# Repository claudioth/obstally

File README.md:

# OBS Tally & Control
OBS Tallylights via OBS-Websockets and GPIOzero.

This Toolset was written to support sundays-church-streaming

## Simplicity
On church a lot of work is done by voluntiers, so we can not exspect deep
network and computer knowhow. 

So the tool is written automatically fix problems as much as possible.

Example:
* problem: the network connection to OBS ist lost
* auto-reaction: try to reconnect to OBS automaticaly

## Enviroment
The tool was written for the following context:
* runs on a raspberry pi (or probably any linux computer)
* OBS ist best used in "studio mode", but "none studio" should also work
  (but will not react when changing visibility of sources of a scene in program)

## Features
* configuration by real XML, not depenting on tag ordering
* LEDs status can be configured in dependence of scenes and/or sources
* support unlimited amount of scene and sources
* after startup LEDs will proactive be set conforming actual OBS status
  (will not wait for first switch/preview event)
* connection to OBS is monitored and will try to reconnect if lost
* start order is uncritical, OBS can be (re-)started anytime
* if not connected all CAM LEDs are switched on
* (optional) connection status can be visualized by an extra LED

## LED colors
LED colors depends (of course) on your personal hardware configuration.

Wie use a blue LED to visualise the connection status:
* blinking: not connected, trying to reconnect
* permanently glowing: connected

We use for each CAM, 2 LEDs with following colors:
* red LED for "in program"
* orange LED for "in preview"

### possible LEDs glowing combinations
The behavior is configurable. You can choose one of the following, conforming 
your preference and needs:

* (A) basic:in basic-mode any conbination is possible, also both LEDs on at the same time
    - CAM in programm => red LED glowing
    - CAM in preview => orange LED glowing

* (B) max. 1 LED per CAM enabled: same as (A), but in case a CAM is also "in preview", only the
    "in program" LED will be enabled

* (C) max. 1 LED type enabled: same as (B), but maximal 1 LED type will be enabled at the same time.
    examples:
     - CAM 1 in program AND CAM 2 in preview: only LED for CAM 1 will be enabled
     - unknown scene/source in program AND CAM 1 in preview: CAM 1 LED shown
     - CAM 1 and CAM 2 in program, CAM 3 in preview: CAM 1+2 will be enabled
     - unknown scene/source in program AND CAM 1+2 in preview: CAM 1+2 LED shown

### Installation
### automated
In the sufolder "install" is a script that can be used for automatical installation

#### manually
If you prefere to install it manually, here a list of todos:
* install all needed third-party-software

```shell
apt update
apt install nginx php-fpm php-xml python-gpiozero
pip install obs-websocket-py
git checkout https://github.com/claudioth/obstally
```
* setup your NGINX to support PHP-scripts
* link or copy the content of the "www" subfolder to your webfolder

```shell
mkdir /var/www/html/tally/
cp -r ./www/* /var/www/html/tally/
```
* Call the index.php from your browser to configure this tool

    http://localhost/tally/

* Setup OBS-Tally Settings (IP, password, port from OBS-Websockets, scenes, sources and GPIO-Ports)
* Connect LEDs to the matching GPIO and try
* If you want to use OBSTally with an relais-card, you need to use the Inverted-Version
* install this script as a service to automatically startup when booting your raspberry

### Configuration
The configuration is done by editing the XML-file.

**Attention:** each GPIO port can only be used *once*

**Hint:** the GPIO port can also be inverted. Just add an attribute to the tag 
(`inverted="true"`) or simple set a - before the GPIO number.

#### obswebsocket
Here are the connection settings to OBS defined
* `host`: The hostname or IP-address to connect to
    - in case an attribute `network` is given, the host value will only be used, if the own IP matches to the given network.
    All not matching networks will be ignored.
    - A mix of both is possible, if not matching network was found, than the value without attribute will be used as fallback.
	  
* `port`: (optional) the port to be used for connection, by default 4444
* `pass`: (optional) a password for connection authentication, default is empty
* `gpio_connected`: a GPIO number where a LED could be connected to visualise
  the connection-status:
    - *off*: service ist not running
    - *flashing*: trying to connect to OBS
    - *on*: connected to OBS

```xml
	<obswebsocket>
		<host>192.168.2.137</host> <!-- default host -->
		<!-- but the following would be used if network matches -->
		<host network="192.168.10">192.168.10.137</host>
		<port>4444</port>
		<pass/>
		<gpio_connected>19</gpio_connected>
	</obswebsocket>
```

#### scene
You can define several scene to LED combinations. Each scene is defined by:
* `name`: then name of the OBS scene
* `gpio_preview`: a GPIO number where a LED is connected to show,
  that the scene is actualy been shown in the "preview". 
* `gpio_program`: a GPIO number where a LED is connected to show,
  that the scene is actualy been shown in the "program". 

```XML
	<scene>
		<name>HDMI 1</name>
		<gpio_preview>2</gpio_preview>
		<gpio_program>3</gpio_program>
	</scene>
	<scene>
		<!-- example for use inverted signals -->
		<name>HDMI 2</name>
		<gpio_preview>-4</gpio_preview>
		<gpio_program inverted="true">5</gpio_program>
	</scene>
```

#### source
You can define several source to LED combinations. Each source is defined by:
* `name`: then name of the OBS source
* `gpio_preview`: a GPIO number where a LED is connected to show,
  that the scene is actualy been shown in the "preview". 
* `gpio_program`: a GPIO number where a LED is connected to show,
  that the scene is actualy been shown in the "program". 

```XML
	<source>
		<name>PTZ1</name>
		<gpio_preview>26</gpio_preview>
		<gpio_program>6</gpio_program>
	</source>
	<source>
		<!-- example for use inverted signals -->
		<name>PTZ2</name>
		<gpio_preview>-20</gpio_preview>
		<gpio_program inverted="true">12</gpio_program>
	</source>
```
### License
This program is free software: you can redistribute it and/or modify
it under the terms of the GNU General Public License as published by
the Free Software Foundation, either version 3 of the License, or
(at your option) any later version.

This program is distributed in the hope that it will be useful,
but WITHOUT ANY WARRANTY; without even the implied warranty of
MERCHANTABILITY or FITNESS FOR A PARTICULAR PURPOSE.  See the
GNU General Public License for more details.

You should have received a copy of the GNU General Public License
along with this program.  If not, see <http://www.gnu.org/licenses/>.

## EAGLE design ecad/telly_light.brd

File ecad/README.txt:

Example board using Eagle CAD (https://www.autodesk.com/products/eagle/overview)

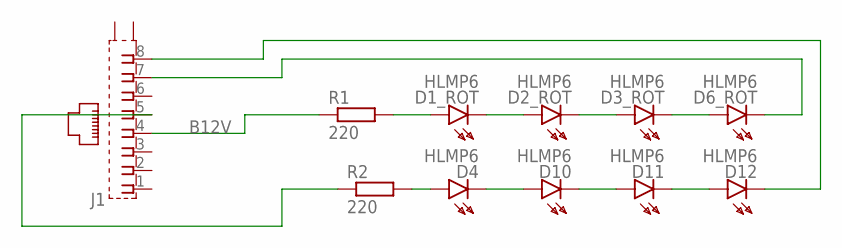
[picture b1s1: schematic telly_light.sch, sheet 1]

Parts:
D1_ROT, D2_ROT, D3_ROT, D4, D6_ROT, D10, D11, D12: HLMP6
J1: 555153-1
R1, R2: 220; 0204/7

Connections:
B12V: J1.5, R2.1
unnamed: D1_ROT.A, R1.2
unnamed: D1_ROT.K, D2_ROT.A
unnamed: D2_ROT.K, D3_ROT.A
unnamed: D3_ROT.K, D6_ROT.A
unnamed: D4.K, D10.A
unnamed: D10.K, D11.A
unnamed: D11.K, D12.A
unnamed: D4.A, R2.2
unnamed: J1.4, R1.1
unnamed: D12.K, J1.8
unnamed: D6_ROT.K, J1.7

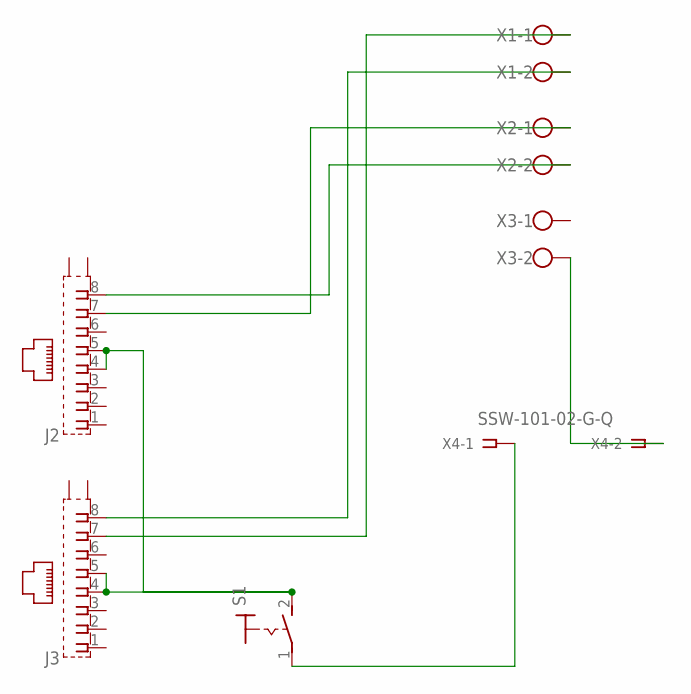
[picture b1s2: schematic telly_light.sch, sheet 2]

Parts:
J2, J3: 555153-1
S1: MS243
X1, X2, X3: W237-102
X4: SSW-101-02-G-Q

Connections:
unnamed: X3.2, X4.2
unnamed: S1.1, X4.1
unnamed: J2.7, X2.1
unnamed: J2.4, J2.5, J3.4, J3.5, S1.2 (S)
unnamed: J2.8, X2.2
unnamed: J3.8, X1.2
unnamed: J3.7, X1.1

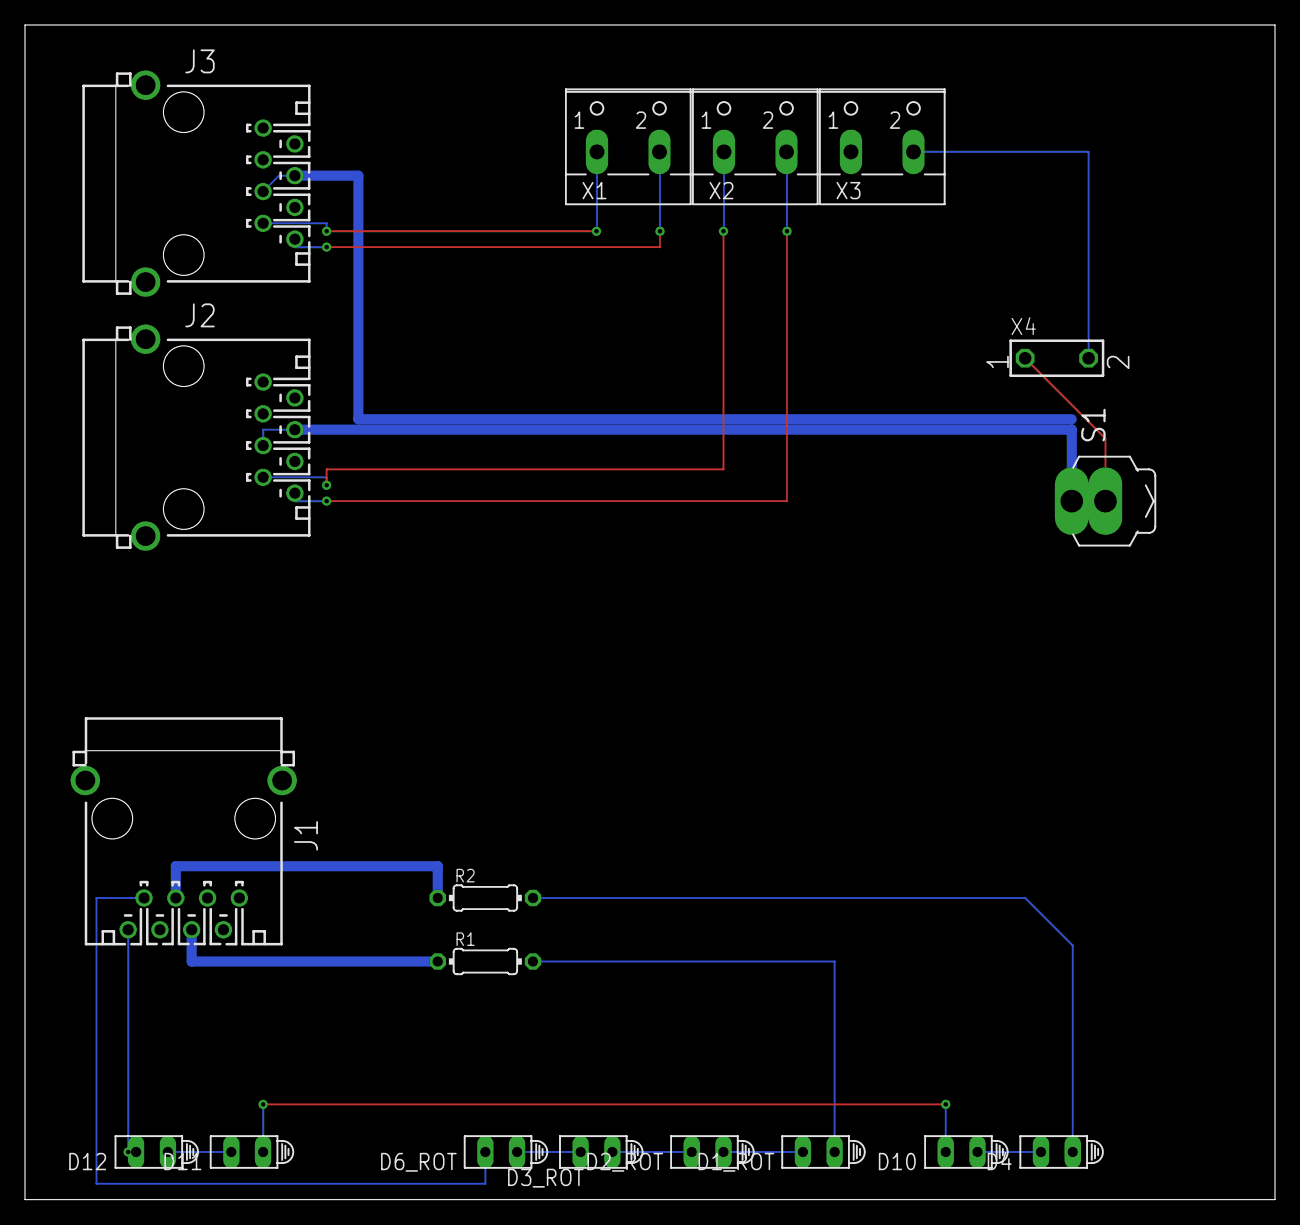
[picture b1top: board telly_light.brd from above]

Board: 2 copper layers, 100.0 x 94.0 mm, 18 parts (0 on the bottom side), 19 nets.

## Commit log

2020-12-26 first commit, basic xml reader
2020-12-26 basic LED initialisation
2020-12-26 add basic OBSwebsocket connection
2020-12-26 add event registration and LED switching
2020-12-26 enable LED directly on startup if scenes are shown
2020-12-26 prevent of using save gpio more then once in config
2020-12-26 fix: Umlauten in scene names
2020-12-26 add support of sources in scenes
2020-12-26 enable LED directly on startup if sources are shown
2020-12-26 code review, function unchanged
2020-12-26 new feature: Same CAM can not be preview and program at the same time
2020-12-26 feature: maximal one LED enabled at the same time
    program LED has priority
2020-12-26 code review and bugfix (reaction on sources was broken)
    scene switching was working but reaction on sources was broken
2020-12-31 code review, function unchanged
    avoid use of "datain"
2020-12-31 removed RPi.GPIO, add only LED
2020-12-31 add connection monitoring
2021-01-01 add socket reconnection when lost
2021-01-01 fix: after one loose of connection, endless reconnections
2021-01-01 add author, copyright infos and readme-file
2021-01-01 code review, split into multiple files
2021-01-01 on disconnect: switch alls LEDs on
2021-01-01 new events: on_disconnect() and on_reconnect()
2021-01-01 code review, class renamed
2021-01-02 wsclient: add signal processing (SIGHUP, SIGINT, SIGTERM) & reload xml
2021-01-02 tally: switch off and remove all LEDs before XML reload
2021-01-28 update README documentation
2021-01-29 add network depended config
2021-01-30 add gitignore
2021-01-30 xml: recognise malformed config
2021-01-30 xml: Add support for inverted tally lights
2021-01-30 xml: support for inverted tally lights (fix)
2021-04-03 fix typos
2021-04-03 add example e-board
